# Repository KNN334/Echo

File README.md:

# CAMUS 左心室视频分割与逐帧容积估算

**DRA-UNet** 是本项目的最终左心室分割模型。模型沿用 Attention-UNet 的跳连门控，在编码器引入空洞残差块，在最深层融合时间上下文，并在解码末端加入边缘监督。训练只对专家标注的 ED/ES 帧计算分割与边缘损失。推理按时间顺序处理 CAMUS 超声 cine 的每一帧，预测掩膜用于后续容积和心功能指标计算。

## 在线左室分割

打开「影像分割」，上传已去标识的心尖二腔心或四腔心超声影像。支持 MP4、AVI、PNG 和 JPEG。DRA-UNet 在服务器逐帧推理，网页显示进度，并排回放原始灰阶影像和左室腔预测掩膜。侧向声束会在推理前自动校正，同一视频使用同一方向，预测掩膜会映回原图方向。在线分割用于研究展示。 [EchoLab 在线分割](https://knn334.github.io/Echo/#/segment)

在用户指定的 `test_images` / `test_masks` 目录中，以 100 张配对图像的左室腔标注在原始分辨率下复核。模型权重固定，按图像平均。

| 推理预处理 | Dice | IoU | Dice < 0.5 的图像数 |
| --- | ---: | ---: | ---: |
| 原方向直接缩放 | 0.0789 | 0.0465 | 98 / 100 |
| 侧向声束对齐并逆变换 | 0.9549 | 0.9141 | 0 / 100 |

这批数据未附患者对应表，因此仅报告图像级方向回归结果。 [复核命令与部署](backend/README.md#验证)

## 文字流程图

```text
CAMUS 原始多帧超声视频：同一患者的 2CH / 4CH 独立 cine
附带原始像素间距、时间信息和专家 ED / ES 掩膜
    ↓
原始文件校验 → 预处理并保留原始标注、坐标变换和元数据
    ↓
固定患者级划分：训练 400 人 / 验证 50 人 / 测试 50 人
    │
    ├─ 模型训练与选择
    │   仅对训练 / 验证患者的 ED / ES 目标帧计算监督损失
    │       ↓
    │   UNet / Attention-UNet / UNet++ / UNet-mini / VGG16-UNet
    │   每个模型独立训练 5 次，归一化参数只由训练数据确定
    │       ↓
    │   每次训练保存验证损失最低的权重
    │   按这些权重的跨种子验证 Dice 均值选择基线
    │   以 Attention-UNet 为对照完成模块消融 → DRA-UNet
    │
    ├─ DRA-UNet 单病例预览：A2C 逐帧分割与 A2C / A4C 掩膜对比
    │
    └─ 五种基线定量评价：固定测试集
        每段视频按原始时间顺序逐帧分割，包括全部无标签帧
            ↓
        二值左室掩膜 → 还原原图尺寸 → 像素间距换算为 mm
            ↓
        PCA 估计长轴 → 沿长轴划分 20 层 → 单平面 Simpson 容积
        2CH 与 4CH 分别计算，不按帧号直接合并
            ↓
        所有帧的容积按真实时间排列，绘制 V(t) 曲线
            ├─ 预测曲线峰谷 → EDV / ESV → 有效配对时计算 SV / EF
            ├─ 完整周期 + 可靠时间 + 相邻 EDV 峰 → T / HR / CO
            │   条件不足时保留 null 和原因，不反射或拼接半周期
            └─ 有专家标签的帧 → 分割指标 + 同几何法容积一致性评价
                无标签帧不计算参考误差，但保留其分割结果与容积
```

模型、权重和阈值在测试前确定。二值化阈值为 0.5，逐帧预览使用各模型 2026 种子的权重。

## DRA-UNet 模型结构

共享编码器处理当前帧及最多两帧历史。最深层 ConvLSTM 跳过序列开头的补位帧，输出经投影后与当前帧瓶颈特征相加。四条跳连只传当前帧的特征，分别由对应解码特征门控。训练时使用专家掩膜计算分割 BCE、Soft Dice 损失、边缘 BCE 和预测掩膜的 Sobel 梯度损失。逐帧容积计算使用分割头生成的掩膜。[模型代码](lvseg/models/ablation.py) · [损失函数](lvseg/losses.py)

## 结果预览

### DRA-UNet 逐帧左心室分割

使用固定测试患者 `patient0015` 的 A2C cine。绿色为 DRA-UNet 预测掩膜，琥珀色轮廓仅在专家标注的 ED 和 ES 帧显示。GIF 为慢速预览，MP4 保留源帧率。[源帧率 MP4](reports/lvseg_ablation/assets/dra_patient0015_2CH.mp4) · [素材来源与权重校验](reports/lvseg_ablation/assets/provenance.json)

<details>
<summary>查看同病例的 Attention-UNet 基线视频</summary>

[源帧率 MP4](reports/lvseg_baselines/assets/best_model_patient0015_2CH.mp4)

</details>

### 同一患者的六模型掩膜网格对比

2×4 网格展示同一患者 A2C 的舒张末期（ED，帧索引 0）。B 超输入上的琥珀色轮廓和右侧白色专家掩膜均来自 CAMUS 的原始 ED 标注。五个基线与 DRA-UNet 的掩膜均为对该帧的二值预测。

<details>
<summary>展开同一布局的全视频逐帧对比</summary>

专家掩膜仅在 ED 和 ES 帧显示。[源帧率 MP4](reports/lvseg_ablation/assets/six_model_patient0015_2CH.mp4)

</details>

### 同一患者 A4C / A2C 双切面的模型掩膜对比

同一测试患者的 A4C（CAMUS 记为 4CH）与 A2C（2CH）分别展示专家标注的 ED 和 ES 帧。每行依次为 B 超输入、专家掩膜、五个基线与 DRA-UNet。两个切面独立采集，各自按原始相位标注取帧。[双切面 PDF](reports/lvseg_ablation/assets/multiview_masks_patient0015.pdf) · [六模型网格 PDF](reports/lvseg_ablation/assets/six_model_patient0015_2CH.pdf)

影像素材来自 CAMUS，采用 CC BY-NC-SA 4.0。[数据署名与许可](docs/data_sources/CAMUS_LICENSE_TERMS.md)

### 五种基线分割结果

五种基线在固定患者划分下各独立训练 5 次。按跨种子的验证集 Dice 均值选择基线；测试集不用于选模。表中验证 Dice 与测试指标均为跨种子均值；每次测试指标先在患者内平均，再汇总。mIoU 是前景与背景 IoU 的均值，HD95/ASD 使用原始像素间距换算为 mm。测试集 ED/ES 标注帧用于分割评价，整段视频（包括无标签帧）都参与推理和容积曲线。

<!-- SEGMENTATION_METRICS_TABLE_START -->

| 模型 | 验证集 Dice | 测试 Dice | 测试 mIoU | Precision | Recall | HD95 (mm) | ASD (mm) |
|---|---:|---:|---:|---:|---:|---:|---:|
| UNet | 0.9298 | 0.9355 | 0.9346 | 0.9444 | 0.9316 | 4.06 | 1.49 |
| **Attention-UNet** ✓ | 0.9300 | 0.9363 | 0.9353 | 0.9432 | 0.9340 | 3.74 | 1.43 |
| UNet++ | 0.9296 | 0.9349 | 0.9340 | 0.9373 | 0.9379 | 3.98 | 1.48 |
| UNet-mini | 0.8880 | 0.9025 | 0.9035 | 0.9026 | 0.9114 | 10.76 | 2.82 |
| VGG16-UNet | 0.9243 | 0.9321 | 0.9311 | 0.9351 | 0.9344 | 4.10 | 1.53 |

<!-- SEGMENTATION_METRICS_TABLE_END -->

完整均值见 [模型对比 CSV](reports/lvseg_baselines/model_comparison.csv)；逐次实验结果、验证集选择记录和离散程度见 [重复实验报告](reports/lvseg_baselines/repeated_runs.json) 与 [结果报告](reports/lvseg_baselines/RESULTS.md)。

### DRA-UNet 模块消融

表中为 CAMUS 验证集 50 名患者的三种子均值（2026、2027、2028）。B 为本轮同训练配置下重训的 Attention-UNet。S 表示用 SE 替换 Attention Gate，D 表示空洞残差编码器，T 表示瓶颈 ConvLSTM，E 表示边缘分支与 Sobel 损失。DRA-UNet 对应 DTE 配置，完整测试集指标尚未汇总。

<!-- DRA_ABLATION_TABLE_START -->

| 配置 | Dice | mIoU | Precision | Recall | HD95 (mm) | ASD (mm) | Simpson MAE (mL) | 配对 ΔDice |
|---|---:|---:|---:|---:|---:|---:|---:|---:|
| B | 0.9287 | 0.9280 | 0.9294 | 0.9328 | 4.28 | 1.57 | 7.96 | +0.0000 |
| S | 0.9284 | 0.9278 | 0.9396 | 0.9221 | 4.22 | 1.55 | 7.90 | -0.0003 |
| D | 0.9311 | 0.9301 | 0.9328 | 0.9336 | 4.11 | 1.50 | 7.97 | +0.0024 |
| T | 0.9309 | 0.9301 | 0.9287 | 0.9375 | 4.20 | 1.51 | 7.88 | +0.0022 |
| E | 0.9298 | 0.9292 | 0.9367 | 0.9273 | 4.15 | 1.52 | 7.98 | +0.0011 |
| SD | 0.9292 | 0.9284 | 0.9272 | 0.9364 | 4.09 | 1.53 | 8.50 | +0.0005 |
| SDT | 0.9298 | 0.9290 | 0.9288 | 0.9356 | 4.11 | 1.52 | 8.28 | +0.0011 |
| SDTE | 0.9299 | 0.9292 | 0.9258 | 0.9389 | 4.11 | 1.52 | 8.06 | +0.0013 |
| **DRA-UNet (DTE)** | 0.9333 | 0.9322 | 0.9396 | 0.9309 | 3.88 | 1.44 | 7.59 | +0.0046 |
| STE | 0.9276 | 0.9268 | 0.9325 | 0.9274 | 4.35 | 1.57 | 8.02 | -0.0011 |
| SDE | 0.9310 | 0.9301 | 0.9345 | 0.9323 | 3.99 | 1.48 | 8.10 | +0.0023 |

<!-- DRA_ABLATION_TABLE_END -->

DRA-UNet 相比 B 的验证 Dice 提高 0.0046，HD95 从 4.28 mm 降至 3.88 mm。配对图按相同种子比较两个配置，患者级图对每位患者的三次配对差值取均值。[完整消融结果](reports/lvseg_ablation/RESULTS.md) · [收敛曲线](reports/lvseg_ablation/evidence/DTE_vs_B/convergence.png) · [输入时间上下文对照](reports/lvseg_ablation/evidence/DTE_vs_B/context_dice.png)

### 逐帧容积波形与时相

图中使用 Attention-UNet 基线的逐帧分割掩膜，按原始图像间距计算 20 圆盘单平面 Simpson 容积并按时间绘制。实心标记为预测容积曲线检测出的 EDV 峰与 ESV 谷，空心标记为专家 ED/ES 参考帧。

CAMUS 提供半周期片段，没有相邻两个 EDV 峰，因此该数据的 HR 和 CO 保留为空。2CH 与 4CH 是不同步采集的序列，不合并计算双平面容积。

### 不同模型的容积估算误差

图中按视图比较五种基线在每名测试患者有标注帧上的平均绝对容积差。预测轮廓和专家掩码使用同一个单平面 Simpson 几何法。

## 容积计算方法

### 逐帧空间标定与 PCA 主轴估计

模型对每一帧输出左室概率图，以 0.5 为阈值得到二值掩膜，再用最近邻插值还原原始图像尺寸。设原图横向、纵向像素间距为 $`s_x`$、$`s_y`$（mm/pixel），前景像素 $`(x_j,y_j)`$ 对应的物理坐标为：

$$
\mathbf{p}_j=(x_js_x,\ y_js_y)^{\mathsf T}.
$$

对这些物理坐标中心化后进行 PCA，以最大特征值对应的特征向量作为长轴方向 $`\mathbf{u}`$，其垂直方向为短轴方向 $`\mathbf{v}`$。长轴投影的最大值与最小值之差为该帧长度 $`L_t`$。PCA 使用预测轮廓本身，不读取专家掩膜或人工心尖、瓣环关键点；它给出的是轮廓派生的主轴估计。

### 单平面 Simpson 圆盘求和

沿长轴将左室划分为 $`N=20`$ 个等厚圆盘，厚度为 $`\Delta L_t=L_t/N`$。第 $`i`$ 层的直径 $`D_{t,i}`$ 由该层掩膜沿短轴方向的投影跨度估计；当前实现额外加上 $`\min(s_x,s_y)`$ 的像素宽度修正，空层直径记为 0。

单切面无法直接测得另一方向的盘径，当前方法假设每层横截面为圆形，得到：

$$
V_t=\frac{1}{1000}\sum_{i=1}^{N}\frac{\pi}{4}D_{t,i}^{\,2}\Delta L_t
\qquad (\mathrm{mL}).
$$

其中直径和厚度均以 mm 计，除以 1000 将 mm³ 转换为 mL。这是 Simpson 圆盘求和几何估计；单平面圆形横截面假设会带来几何误差。

每帧都执行以上计算，再以原始时间戳组成 $`\{(t_k,V_k)\}`$。没有时间戳但有可靠帧率 $`f`$ 时使用 $`t_k=k/f`$。**无标签帧同样参与分割、容积计算与曲线绘制**；空掩膜或无效几何输出缺失值，不用 0 代替真实容积。若缺少空间标定，只保留明确标为 `pixel3_proxy` 的几何代理量，不报告 mL 绝对容积。

### 双切面与双平面方法的关系

当前 CAMUS 的 A4C（4CH）与 A2C（2CH）是独立采集序列，主评价流程分别计算单平面容积。双切面对比图中的 ED/ES 也按各自元数据选取，不表示两个视频逐帧同步。

代码预留了双平面 Simpson 接口，但尚未接入主评价流程。若后续完成两个切面的空间标定、同一时相配对以及心尖至基底方向和盘位对应，每层可按椭圆截面计算：

$$
V_t^{\mathrm{bi}}=\frac{1}{1000}\sum_{i=1}^{N}
\frac{\pi}{4}D_{t,i}^{\mathrm{A4C}}D_{t,i}^{\mathrm{A2C}}\Delta L_t.
$$

这里两个直径必须属于对应时相、对应盘位；当前预留接口以两切面长轴的较小值确定共同盘厚。连续双平面波形还需验证逐帧时间对应。PCA 只估计切面内主轴，不能完成视频同步或保证解剖盘位配准。

实现位置：[容积几何计算](lvseg/metrics/volume.py) · [逐帧推理与原图坐标还原](lvseg/evaluate.py)。

## 心功能指标计算方法

### 容积曲线的峰谷与时相

峰谷检测只读取预测容积和时间，不读取专家 ED/ES 标签。当前实现按连续有效片段检测峰谷，以该片段容积变化范围的 4% 设置显著性阈值；符合条件的片段端点也可作为候选峰谷。内部峰检测按默认最短周期 0.30 s 设置最小峰间距，端点候选另行判断。

对一个候选 EDV 峰，在它与下一候选峰之间选择最低的后续谷作为 ESV；如果没有下一峰，则只在已有片段的后续部分寻找谷。只有满足 $`0<\mathrm{ESV}<\mathrm{EDV}`$ 的时序配对才生成有效事件。

EDV 峰至后续 ESV 谷对应容积下降阶段；ESV 谷至下一 EDV 峰对应容积上升阶段。曲线显示预测 EDV/ESV 标记，并单独显示专家参考时相。这里依据容积识别时相，不据此推断缺少独立标注的瓣膜事件或等容分期。

### 指标公式与单位

设第 $`k`$ 个有效事件的峰、谷时刻分别为 $`t_{\mathrm{ED},k}`$、$`t_{\mathrm{ES},k}`$：

| 指标 | 计算方式 | 单位与条件 |
|---|---|---|
| EDV，舒张末期容积 | $`\mathrm{EDV}_k=V(t_{\mathrm{ED},k})`$ | 空间标定有效时为 mL |
| ESV，收缩末期容积 | $`\mathrm{ESV}_k=V(t_{\mathrm{ES},k})`$ | 同一有效事件中的后续谷，单位 mL |
| SV，每搏量 | $`\mathrm{SV}_k=\mathrm{EDV}_k-\mathrm{ESV}_k`$ | mL/beat；需要有效峰谷配对和空间标定 |
| EF，射血分数 | $`\mathrm{EF}_k=\mathrm{SV}_k/\mathrm{EDV}_k`$ | 无量纲；代码输出 `EF_percent`，即该比值乘 100% |
| T，心动周期 | $`T_k=t_{\mathrm{ED},k+1}-t_{\mathrm{ED},k}`$ | s；需要相邻两个 EDV 峰及已确认的完整周期 |
| HR，心率 | $`\mathrm{HR}_k=60/T_k`$ | bpm；需要可靠时间和有效完整周期 |
| CO，心输出量 | $`\mathrm{CO}_k=\mathrm{SV}_k\times\mathrm{HR}_k`$ | SV 以 mL 计时为 mL/min；再除以 1000 得 L/min |

当前完整周期的可接受范围默认为 0.30–2.50 s，可在评价配置中调整。即使检测到两个峰，来源序列也必须已确认包含完整周期，才计算 HR；绝对 CO 还必须具有空间标定。缺少空间标定时，SV 等几何派生量沿用代理单位，不解释为临床 mL 或绝对 CO。

CAMUS 半周期片段的 HR/CO 保留为空；仅当片段内存在有效 EDV→ESV 时序配对时报告相应 SV/EF。不能形成配对时相关结果同样保留为空，不倒序、反射或拼接视频制造周期。缺失原因随结果保存；无独立参考时不报告 HR/CO 的临床准确率。

实现位置：[峰谷检测与心功能指标](lvseg/metrics/cycles.py) · [容积曲线绘制](lvseg/visualization/volume_curve.py)。

## 分割与容积评价指标

### 分割重叠指标

仅在有专家标签的测试帧上，将预测左室掩膜 $`P`$ 与原始专家掩膜 $`G`$ 在相同原图坐标中比较。TP 为正确预测的左室像素，FP 为误判为左室的背景像素，FN 为漏检的左室像素，TN 为正确预测的背景像素。

| 指标 | 计算公式 | 解释 |
|---|---|---|
| Dice | $`2\mathrm{TP}/(2\mathrm{TP}+\mathrm{FP}+\mathrm{FN})`$ | 前景重叠程度，越高越好 |
| IoU | $`\mathrm{TP}/(\mathrm{TP}+\mathrm{FP}+\mathrm{FN})`$ | 左室前景交并比，越高越好 |
| mIoU | $`(\mathrm{IoU}_{\mathrm{LV}}+\mathrm{IoU}_{\mathrm{BG}})/2`$ | 左室与背景两类 IoU 的均值；背景 IoU 为 $`\mathrm{TN}/(\mathrm{TN}+\mathrm{FP}+\mathrm{FN})`$ |
| Precision | $`\mathrm{TP}/(\mathrm{TP}+\mathrm{FP})`$ | 预测左室中实际属于左室的比例，越高越好 |
| Recall | $`\mathrm{TP}/(\mathrm{TP}+\mathrm{FN})`$ | 实际左室中被检出的比例，越高越好 |

### 边界距离指标

设预测与专家轮廓分别为 $`A=\partial P`$、$`B=\partial G`$，$`d(a,B)`$ 表示轮廓点 $`a`$ 到 $`B`$ 中最近点的欧氏距离，使用原始像素间距换算为 mm。将两个方向的距离样本合并且不去重，记为 $`\mathcal{D}`$：

$$
\mathrm{HD95}=Q_{0.95}(\mathcal{D}),\qquad
\mathcal{D}=\{d(a,B):a\in A\}\mathbin{\uplus}\{d(b,A):b\in B\}.
$$

$$
\mathrm{ASD}=\frac{\sum_{a\in A}d(a,B)+\sum_{b\in B}d(b,A)}{|A|+|B|}.
$$

HD95 为合并双向距离的第 95 百分位，ASD 为按轮廓点数加权的双向平均距离，两者越低越好。任一掩膜为空时 HD95/ASD 为缺失值；无空间标定时只能以 pixel 报告。重叠指标按实现约定处理空掩膜：两者都为空时为 1，仅一者为空时前景 Dice/IoU、Precision/Recall 为 0；mIoU 仍按前景和背景分别计算。

每次实验先在患者内平均各有标签帧的指标，再在患者间平均，最后对 5 个独立种子的结果取均值。HD95/ASD 的缺失值不当作 0，按有效值汇总。README 对比表仅展示均值；基线选择使用验证集 Dice 的跨种子均值，测试集指标不参与选模。

### 容积误差与 Bland–Altman 一致性

对每个有标签帧，分别将预测掩膜和专家掩膜送入**同一个单平面 Simpson 方法**，得到 $`\hat V_j`$ 与 $`V_j^{\mathrm{mask}}`$。当前容积误差图按患者 $`p`$、切面 $`v`$ 汇总其有效标签帧的平均绝对差：

$$
\mathrm{MAE}_{p,v}=\frac{1}{K_{p,v}}\sum_{j=1}^{K_{p,v}}
\left|\hat V_{p,v,j}-V_{p,v,j}^{\mathrm{mask}}\right|.
$$

$`K_{p,v}`$ 为该患者、该切面中预测与专家掩膜容积均有效的标签帧数。空间标定有效时 MAE 以 mL 计，越低越好。图中每个点为一名患者，箱体表示中位数及四分位范围，红色菱形表示均值；该图使用各模型 2026 种子的代表性权重。

Bland–Altman 对每一对有效测量计算横坐标 $`m_j`$ 和差值 $`d_j`$，再计算平均偏差与 95% 一致性界限：

$$
m_j=\frac{\hat V_j+V_j^{\mathrm{mask}}}{2},\qquad
d_j=\hat V_j-V_j^{\mathrm{mask}},\qquad
\mathrm{Bias}=\bar d=\frac{1}{n}\sum_{j=1}^{n}d_j.
$$

$$
s_d=\sqrt{\frac{\sum_{j=1}^{n}(d_j-\bar d)^2}{n-1}},\qquad
\mathrm{LoA}_{\mathrm{lower}}=\bar d-1.96s_d,\qquad
\mathrm{LoA}_{\mathrm{upper}}=\bar d+1.96s_d.
$$

其中 $`n`$ 为有效测量对数，$`s_d`$ 为差值的样本标准差；不足两对时不计算一致性界限。上述 95% 解释以差值分布近似正态等假设为前提。这些界限描述测量差的一致性范围，不是均值的置信区间，也不是“准确率百分比”。

结果分别保留按切面的帧级分析，以及先在每名患者、每个切面内平均标签帧容积、再进行比较的患者级分析。帧级包含同一患者的重复测量，不能把这些帧当成相互独立的患者。当前对照参考是专家掩膜经相同几何法得到的容积，不等同于独立临床容积标签或数据集提供的 EF 标签。

**评价范围：**Dice/IoU 衡量有标签帧的分割质量，容积 MAE/Bland–Altman 衡量这些帧上的同几何法一致性。无标签帧保留在预测曲线中，但缺少逐帧容积参考，当前不能据此宣称整条容积曲线已经获得完整准确性验证。

实现位置：[分割指标](lvseg/metrics/segmentation.py) · [Bland–Altman 计算](lvseg/metrics/cycles.py) · [患者级汇总](lvseg/evaluate.py) · [模型容积误差图](lvseg/visualization/comparison.py)。

## 数据和评价协议

- CAMUS 官方原始数据：500 名患者，3,500 个发布清单文件全部通过 SHA-256 校验；包含 2CH/4CH 多帧 cine、对应标签和时序/空间信息。原始数据遵循 CC BY-NC-SA 4.0，非商业研究使用，需按 [CAMUS 许可与引用说明](docs/data_sources/CAMUS_LICENSE_TERMS.md)署名。
- 处理后数据：1,000 段 cine、19,232 帧；2,000 帧有 ED/ES 专家掩码。固定患者划分为训练/验证/测试 400/50/50，防止同一患者跨集合。
- 对比模型：U-Net、Attention U-Net、U-Net++、U-Net-mini、VGG16-U-Net；模型选择只用验证集，测试集只用于最终评价。
- 测试集共 50 名患者、100 段 cine、1,961 帧。每个模型都推理全部帧，其中 200 帧有标签、1,761 帧无标签。IoU、Dice、Precision、Recall、HD95、ASD 只在有标签帧上计算。
- 容积波形覆盖推理视频的每一帧。容积 Bland–Altman 对照仅使用带专家掩码的测试帧；预测掩码和专家掩码使用相同 Simpson 几何法。
- 原始影像、处理后数组、模型权重及逐帧缓存不提交到 Git；README 展示所需的轻量图像、GIF 和 MP4 作为结果资产纳入仓库。

## 运行

在 Windows 项目根目录使用项目虚拟环境：

```powershell
.venv\Scripts\python.exe scripts\download_camus.py --workers 4
.venv\Scripts\python.exe scripts\prepare_camus.py
.venv\Scripts\python.exe scripts\run_baselines.py --stage all --device cuda
.venv\Scripts\python.exe scripts\run_repeated_baselines.py --seeds 2026 2027 2028 2029 2030 --device cuda
.venv\Scripts\python.exe scripts\export_readme_assets.py
.venv\Scripts\python.exe -m pytest -q
```

无 CUDA 时将 `--device cuda` 改为 `--device cpu`。EchoNet-Dynamic 仅支持在取得数据访问授权后准备；该数据没有空间标定，不用于报告 mL 容积或绝对 CO。

DRA-UNet 使用 `build_model("DRA-UNet")` 构建。消融训练配置、锁定的代码版本和预览导出命令见 [DRA-UNet 复现步骤](docs/dra_unet_reproduction.md)。

EchoLab 网页可连接 FastAPI 查询报表、查看公开病例，并对上传的去标识超声心动图执行 DRA-UNet 分割和逐帧回放。 [Render 部署与模型配置](backend/README.md) · [前端接入](web/README.md)

## 目录

```text
lvseg/                         左室数据、模型、评价、时相和容积
scripts/                       下载、预处理、训练/评价及 README 素材导出
configs/lvseg.yaml             基线模型、数据和评价设置
tests/                         左室分割与心功能指标检查
reports/lvseg_baselines/       结果报告、对比表和 README 展示素材
reports/lvseg_ablation/        DRA-UNet 三种子消融、结构图和预览
backend/                       FastAPI 报表查询、病例详情与影像存档
web/                           EchoLab 网页与公开回放素材
```

工程检查通过不等于贴片系统验证或临床有效性验证。当前 CAMUS 单平面几何结果不应解释为同步双平面或独立临床容积测量。

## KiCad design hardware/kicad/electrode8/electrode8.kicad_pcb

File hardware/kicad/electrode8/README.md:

# 8 阵元电极接点与引出线教学工程

本工程配合 `docs/hardware/` 下的两份中文教程使用。它是用于学习 KiCad 的铜电极接点与布线示例，参数由本次教学设定，不是 Hu 等 Nature 2023 论文的加工图。

- `electrode8.kicad_pro`：双击后在 KiCad 工程管理器打开。
- `electrode8.kicad_sch`：9 路连接关系；CH1–CH8 为独立通道，RET 为公共返回接点。
- `electrode8.kicad_pcb`：24 × 30 mm、仅正面布线的完成示例。
- `PatchLesson.pretty/`、`PatchLesson.kicad_sym`：工程自带的教学封装、符号；不依赖下载第三方库。
- `fp-lib-table`、`sym-lib-table`：使用 `${KIPRJMOD}` 相对路径，可整体复制工程。
- `exports/`：电极铜层 SVG/DXF、Gerber、连接检查报告。
- `../../tools/build_electrode_lesson.py`：重建示例的源文件；会覆盖示例，个人练习请另存工程。

先阅读 [软件使用说明](../../../docs/hardware/01_KiCad中文使用说明.md)，再按 [从零画电极教程](../../../docs/hardware/02_从零绘制电极图教程.md) 在新工程中操作。

RET 表示本练习中的公共返回连接，不自动等同于保护地、人体参考电极或任何实际设备的地。示例没有超声发射、接收、供电、隔离与驱动电路；也未建立压电片、柔性基底、液态金属层和封装的实物堆叠关系。导出文件用于学习导出和图形核对。

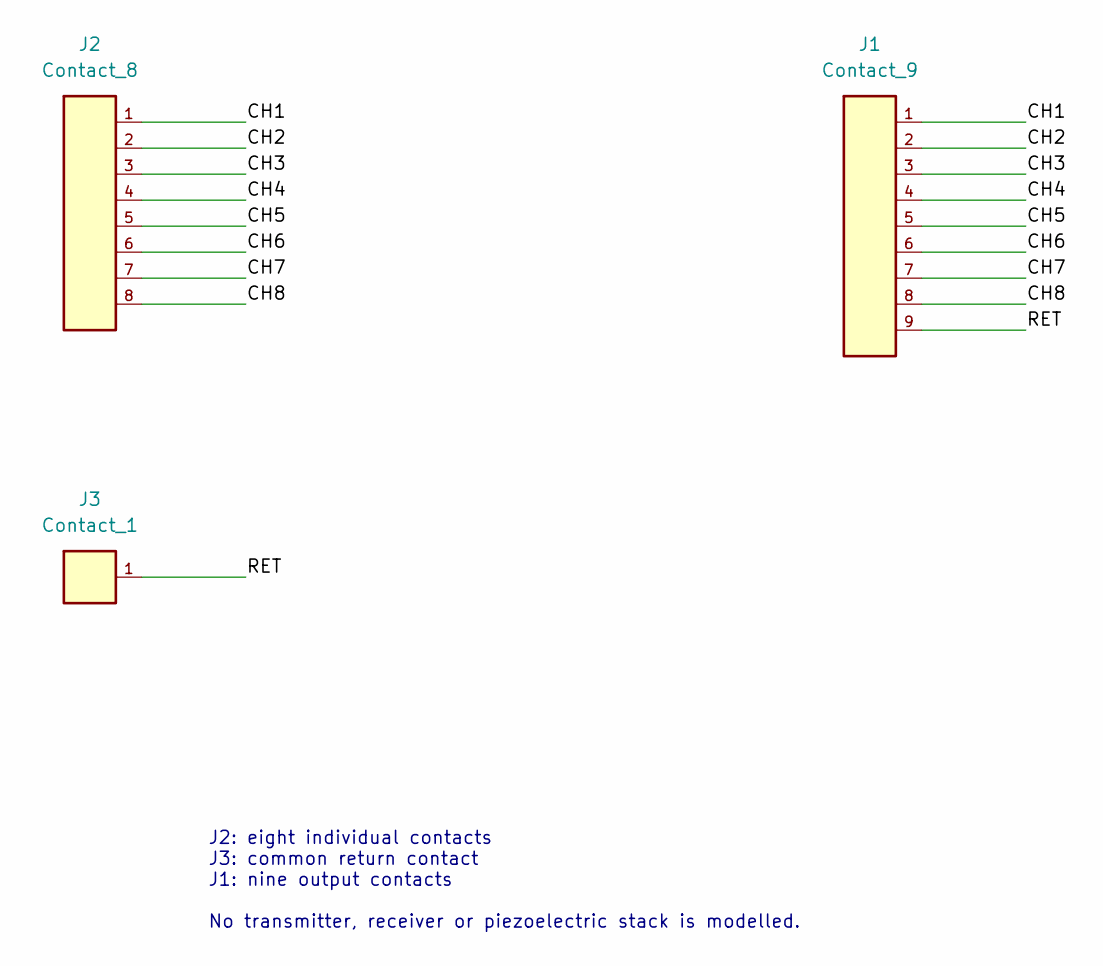
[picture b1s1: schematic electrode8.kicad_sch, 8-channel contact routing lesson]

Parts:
J1: Contact_9; Tail_9_P2.00
J2: Contact_8; Array_8_P1.20
J3: Contact_1; Return_Contact

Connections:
/CH1: J1.1, J2.1
/CH2: J1.2, J2.2
/CH3: J1.3, J2.3
/CH4: J1.4, J2.4
/CH5: J1.5, J2.5
/CH6: J1.6, J2.6
/CH7: J1.7, J2.7
/CH8: J1.8, J2.8
/RET: J1.9, J3.1

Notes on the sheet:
J2: eight individual contacts J3: common return contact J1: nine output contacts No transmitter, receiver or piezoelectric stack is modelled.

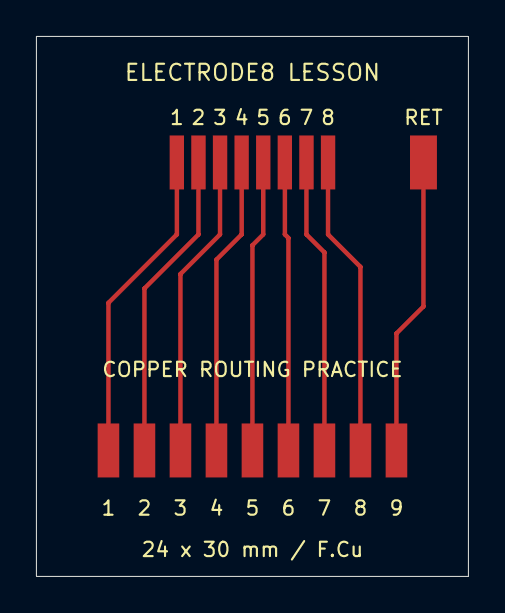
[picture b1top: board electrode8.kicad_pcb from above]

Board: 2 copper layers, 24.0 x 30.0 mm, 3 parts (0 on the bottom side), 9 nets.

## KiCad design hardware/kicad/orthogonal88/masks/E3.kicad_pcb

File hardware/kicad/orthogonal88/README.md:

# 论文正交 88 通道电极重建

打开 [orthogonal88.kicad_pro](orthogonal88.kicad_pro)，进入 PCB 编辑器查看总图，进入原理图编辑器查看电气连接。适用 KiCad 10.0.8。

这是依据 Hu 等 Nature 2023 主文 Extended Data Fig.1、Methods 与补充 Discussion 3.1 / Fig.6 建立的**拓扑与掩模布局重建**。论文未附原始 CAD、逐线坐标、完整端子表，因此本工程没有宣称恢复作者原版加工文件。详细来源、参数边界和手动操作见 [中文复现说明](../../../docs/hardware/03_论文正交88通道复现.md)。

另附[中文说明 PDF](../../../docs/hardware/documents/03_论文正交88通道复现.pdf)和[中文 KiCad 实际界面截图](exports/kicad_chinese_view.png)。

## 文件

- `orthogonal88.kicad_pcb`：四层信号电极、公共返回电极和屏蔽层的总图。User.2 是子阵元轮廓，User.1 是本工程端子编号。显示信号时可隐藏 LM_RETURN / LM_SHIELD。
- `orthogonal88.kicad_sch`：88 个信号接点、2 个返回/屏蔽接点，以及 5 个子页中的 348 个压电子阵元。两端被动符号表达连接关系，没有捏造压电等效电路参数。
- `masks/E1…E4.kicad_pcb`：四张独立信号掩模；每张用 F.Cu 表示一层液态金属图案。
- `masks/RETURN.kicad_pcb`、`masks/SHIELD.kicad_pcb`：公共返回与接地屏蔽的外形示意，含假定的键合接点。
- `channel_map.csv`：88 路通道、图层与本工程端子号；`geometry.json`：接点、引线、压电元件位号的完整关联。
- `logical_axis_groups.json`：U / V 各 32 个逻辑阵元的通道组。中央行/列分组是采集控制关系，**不是永久短路**。
- `exports/`：六层 SVG、毫米制 DXF、总图 SVG、六页原理图 PDF、原始 ERC/DRC、XML 网表及审核结果。

每个信号掩模有 13 × 6 + 9 = 87 个子阵元接点，另有 22 个输出接点。四层共 348 个子阵元接点和 88 个信号输出。输出分为两个斜向接点组；每层接点间距 0.4 mm，两层错位后投影间距 0.2 mm。它不是一个已选型的标准连接器，层间接点的最终露出与键合结构尚未设计。

## 图层约定

| KiCad 标识 | 显示名称 | 本工程含义 |
|---|---|---|
| F.Cu | LM_E1 | U_NEG 的 13 路 + 中央 9 路 |
| In1.Cu | LM_E2 | V_POS 的 13 路 + 中央 9 路 |
| In2.Cu | LM_E3 | U_POS 的 13 路 + 中央 9 路 |
| In3.Cu | LM_E4 | V_NEG 的 13 路 + 中央 9 路 |
| In4.Cu | LM_SHIELD | 接地屏蔽示意 |
| B.Cu | LM_RETURN | 公共底返回电极示意 |

这六个 KiCad 铜层用于存储独立掩模，不表示论文的真实物理层序、介质厚度或普通 FR4 六层板。返回电极在压电材料另一侧，屏蔽层在器件外侧，不能把 KiCad 的层表当作完整器件剖面。

文件中的 1.6 mm 板厚是 KiCad 默认占位值，不是论文器件厚度；3D 预览也不能用于读出真实材料厚度。

## 检查与限制

网表审计：88 信号通道、348 子阵元、89 网络、438 个符号，RETURN 含 350 个引脚节点；每方向 32 个逻辑阵元。ERC 0；六张单层图 DRC 0、未连接 0。总图 DRC 0 错误、199 个 `isolated_copper` 警告，原始报告未屏蔽：内层接点使用无常规焊盘锚点的铜区，独立单层图负责电气连接审核。总图显示的未连接 0 不能用于证明真实层间互连。

另行检查四层所有引线到其他通道接点开窗投影的距离，最小 0.035 mm，超过本工程的 0.03 mm 间距。这只检查名义二维几何，没有验证激光开窗深度、对位公差、SEBS 绝缘厚度、键合和可靠性。

**不能用 F8 将原理图同步为这张掩模总图。** 符号被设为不进入 PCB；总图采用铜区抽象，独立掩模中的接点也不是普通器件封装。没有宣称通过原理图与 PCB 常规封装一致性检查。未提供可直接下单的 Gerber 或普通通孔替代物。

## 重建和复查

在项目根目录，先用普通 Python 生成布局清单，再用 KiCad 自带 Python 构建；会覆盖本目录生成文件，修改练习请先复制到其他工程。

```powershell
python hardware/tools/build_orthogonal_patch.py plan
& "$env:LOCALAPPDATA/Programs/KiCad/10.0/bin/python.exe" -u hardware/tools/build_orthogonal_patch.py build
powershell -NoProfile -ExecutionPolicy Bypass -File hardware/tools/check_orthogonal_patch.ps1
python hardware/tools/render_orthogonal_preview.py
```

预览图需要 Pillow。其余规划与网表审计仅需 Python 标准库，构建需要 KiCad 的 `pcbnew`；检查脚本默认 KiCad 安装于当前用户目录，可用 `-KiCadBin` 指定其他位置。

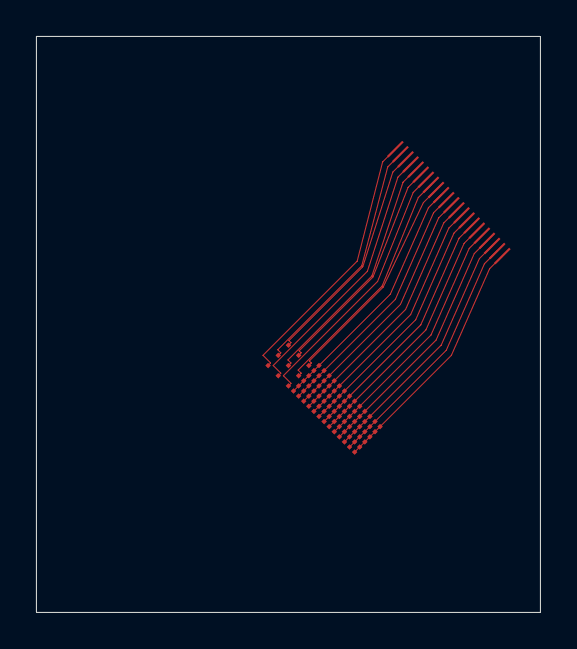
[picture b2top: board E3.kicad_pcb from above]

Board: 2 copper layers, 28.0 x 32.0 mm, 22 parts (0 on the bottom side), 22 nets.

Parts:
P3: C_R6C2
P7: C_R4C2
P11: C_R2C2
P15: C_R6C4
P19: C_R4C4
P23: C_R2C4
P27: C_R6C6
P31: C_R4C6
P35: C_R2C6
P39: U_POS_01
P43: U_POS_02
P47: U_POS_03
P51: U_POS_04
P55: U_POS_05
P59: U_POS_06
P63: U_POS_07
P67: U_POS_08
P71: U_POS_09
P75: U_POS_10
P79: U_POS_11
P83: U_POS_12
P87: U_POS_13

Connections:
C_R2C2: P11.1, P11.2
C_R2C4: P23.1, P23.2
C_R2C6: P35.1, P35.2
C_R4C2: P7.1, P7.2
C_R4C4: P19.1, P19.2
C_R4C6: P31.1, P31.2
C_R6C2: P3.1, P3.2
C_R6C4: P15.1, P15.2
C_R6C6: P27.1, P27.2
U_POS_01: P39.1, P39.2
U_POS_02: P43.1, P43.2
U_POS_03: P47.1, P47.2
U_POS_04: P51.1, P51.2
U_POS_05: P55.1, P55.2
U_POS_06: P59.1, P59.2
U_POS_07: P63.1, P63.2
U_POS_08: P67.1, P67.2
U_POS_09: P71.1, P71.2
U_POS_10: P75.1, P75.2
U_POS_11: P79.1, P79.2
U_POS_12: P83.1, P83.2
U_POS_13: P87.1, P87.2

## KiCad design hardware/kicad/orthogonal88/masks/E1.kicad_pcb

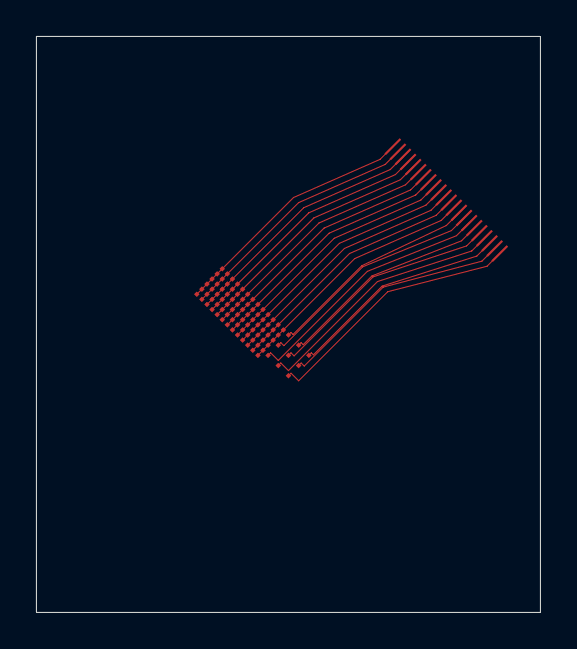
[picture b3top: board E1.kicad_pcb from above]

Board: 2 copper layers, 28.0 x 32.0 mm, 22 parts (0 on the bottom side), 22 nets.

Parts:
P1: U_NEG_01
P5: U_NEG_02
P9: U_NEG_03
P13: U_NEG_04
P17: U_NEG_05
P21: U_NEG_06
P25: U_NEG_07
P29: U_NEG_08
P33: U_NEG_09
P37: U_NEG_10
P41: U_NEG_11
P45: U_NEG_12
P49: U_NEG_13
P53: C_R1C1
P57: C_R3C1
P61: C_R5C1
P65: C_R1C3
P69: C_R3C3
P73: C_R5C3
P77: C_R1C5
P81: C_R3C5
P85: C_R5C5

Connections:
C_R1C1: P53.1, P53.2
C_R1C3: P65.1, P65.2
C_R1C5: P77.1, P77.2
C_R3C1: P57.1, P57.2
C_R3C3: P69.1, P69.2
C_R3C5: P81.1, P81.2
C_R5C1: P61.1, P61.2
C_R5C3: P73.1, P73.2
C_R5C5: P85.1, P85.2
U_NEG_01: P1.1, P1.2
U_NEG_02: P5.1, P5.2
U_NEG_03: P9.1, P9.2
U_NEG_04: P13.1, P13.2
U_NEG_05: P17.1, P17.2
U_NEG_06: P21.1, P21.2
U_NEG_07: P25.1, P25.2
U_NEG_08: P29.1, P29.2
U_NEG_09: P33.1, P33.2
U_NEG_10: P37.1, P37.2
U_NEG_11: P41.1, P41.2
U_NEG_12: P45.1, P45.2
U_NEG_13: P49.1, P49.2

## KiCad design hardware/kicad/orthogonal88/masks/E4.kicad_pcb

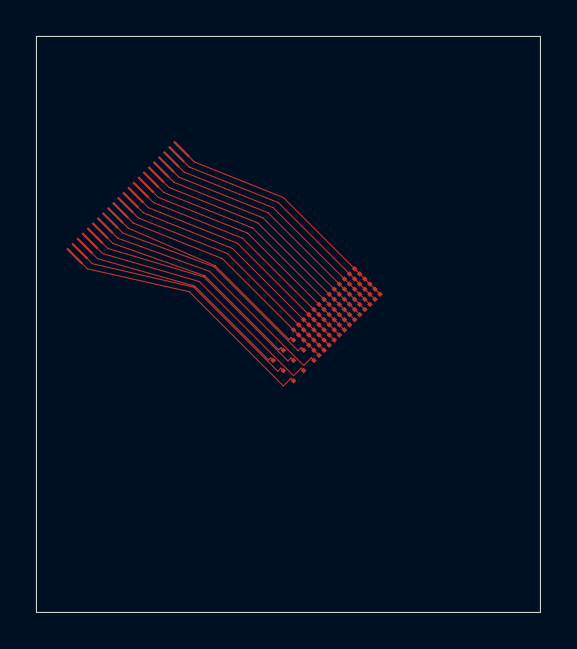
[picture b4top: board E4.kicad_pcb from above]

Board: 2 copper layers, 28.0 x 32.0 mm, 22 parts (0 on the bottom side), 22 nets.

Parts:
P4: V_NEG_01
P8: V_NEG_02
P12: V_NEG_03
P16: V_NEG_04
P20: V_NEG_05
P24: V_NEG_06
P28: V_NEG_07
P32: V_NEG_08
P36: V_NEG_09
P40: V_NEG_10
P44: V_NEG_11
P48: V_NEG_12
P52: V_NEG_13
P56: C_R1C2
P60: C_R1C4
P64: C_R1C6
P68: C_R3C2
P72: C_R3C4
P76: C_R3C6
P80: C_R5C2
P84: C_R5C4
P88: C_R5C6

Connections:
C_R1C2: P56.1, P56.2
C_R1C4: P60.1, P60.2
C_R1C6: P64.1, P64.2
C_R3C2: P68.1, P68.2
C_R3C4: P72.1, P72.2
C_R3C6: P76.1, P76.2
C_R5C2: P80.1, P80.2
C_R5C4: P84.1, P84.2
C_R5C6: P88.1, P88.2
V_NEG_01: P4.1, P4.2
V_NEG_02: P8.1, P8.2
V_NEG_03: P12.1, P12.2
V_NEG_04: P16.1, P16.2
V_NEG_05: P20.1, P20.2
V_NEG_06: P24.1, P24.2
V_NEG_07: P28.1, P28.2
V_NEG_08: P32.1, P32.2
V_NEG_09: P36.1, P36.2
V_NEG_10: P40.1, P40.2
V_NEG_11: P44.1, P44.2
V_NEG_12: P48.1, P48.2
V_NEG_13: P52.1, P52.2

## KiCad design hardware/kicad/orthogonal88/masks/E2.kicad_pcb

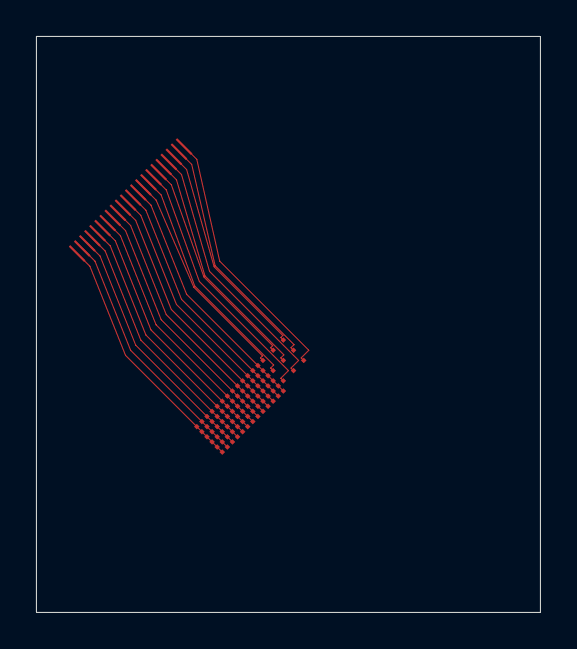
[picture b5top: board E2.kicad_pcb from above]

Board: 2 copper layers, 28.0 x 32.0 mm, 22 parts (0 on the bottom side), 22 nets.

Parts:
P2: C_R2C5
P6: C_R2C3
P10: C_R2C1
P14: C_R4C5
P18: C_R4C3
P22: C_R4C1
P26: C_R6C5
P30: C_R6C3
P34: C_R6C1
P38: V_POS_01
P42: V_POS_02
P46: V_POS_03
P50: V_POS_04
P54: V_POS_05
P58: V_POS_06
P62: V_POS_07
P66: V_POS_08
P70: V_POS_09
P74: V_POS_10
P78: V_POS_11
P82: V_POS_12
P86: V_POS_13

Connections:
C_R2C1: P10.1, P10.2
C_R2C3: P6.1, P6.2
C_R2C5: P2.1, P2.2
C_R4C1: P22.1, P22.2
C_R4C3: P18.1, P18.2
C_R4C5: P14.1, P14.2
C_R6C1: P34.1, P34.2
C_R6C3: P30.1, P30.2
C_R6C5: P26.1, P26.2
V_POS_01: P38.1, P38.2
V_POS_02: P42.1, P42.2
V_POS_03: P46.1, P46.2
V_POS_04: P50.1, P50.2
V_POS_05: P54.1, P54.2
V_POS_06: P58.1, P58.2
V_POS_07: P62.1, P62.2
V_POS_08: P66.1, P66.2
V_POS_09: P70.1, P70.2
V_POS_10: P74.1, P74.2
V_POS_11: P78.1, P78.2
V_POS_12: P82.1, P82.2
V_POS_13: P86.1, P86.2
